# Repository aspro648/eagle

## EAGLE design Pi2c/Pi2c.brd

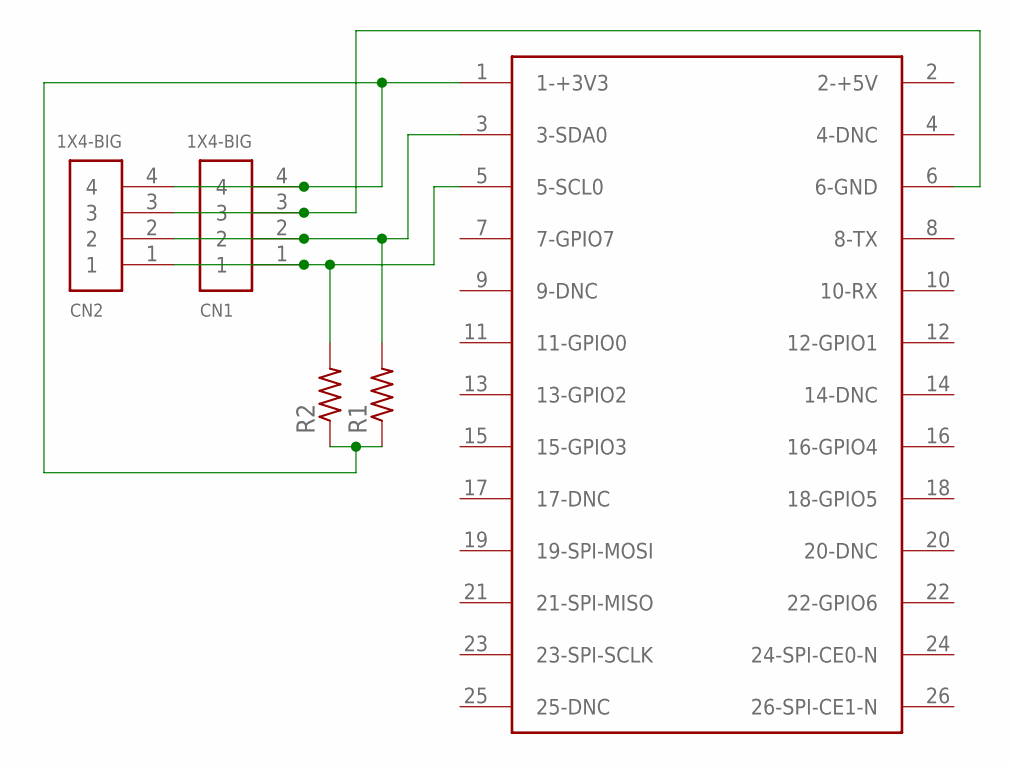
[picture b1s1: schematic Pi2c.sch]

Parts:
CN1, CN2: 1X4-BIG; 1X04-BIG
R1, R2: R-US_0207/7; 0207/7
U$1: RASPBERRY-PI

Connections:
unnamed: CN1.4, CN2.4, R1.1, R2.1, U$1.1 (1-+3V3)
unnamed: CN1.3, CN2.3, U$1.6 (6-GND)
unnamed: CN1.2, CN2.2, R1.2, U$1.3 (3-SDA0)
unnamed: CN1.1, CN2.1, R2.2, U$1.5 (5-SCL0)

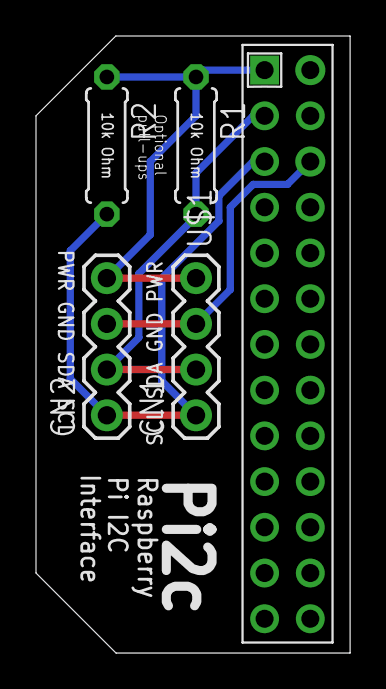
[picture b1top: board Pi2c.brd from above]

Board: 2 copper layers, 17.5 x 34.3 mm, 5 parts (0 on the bottom side), 4 nets.

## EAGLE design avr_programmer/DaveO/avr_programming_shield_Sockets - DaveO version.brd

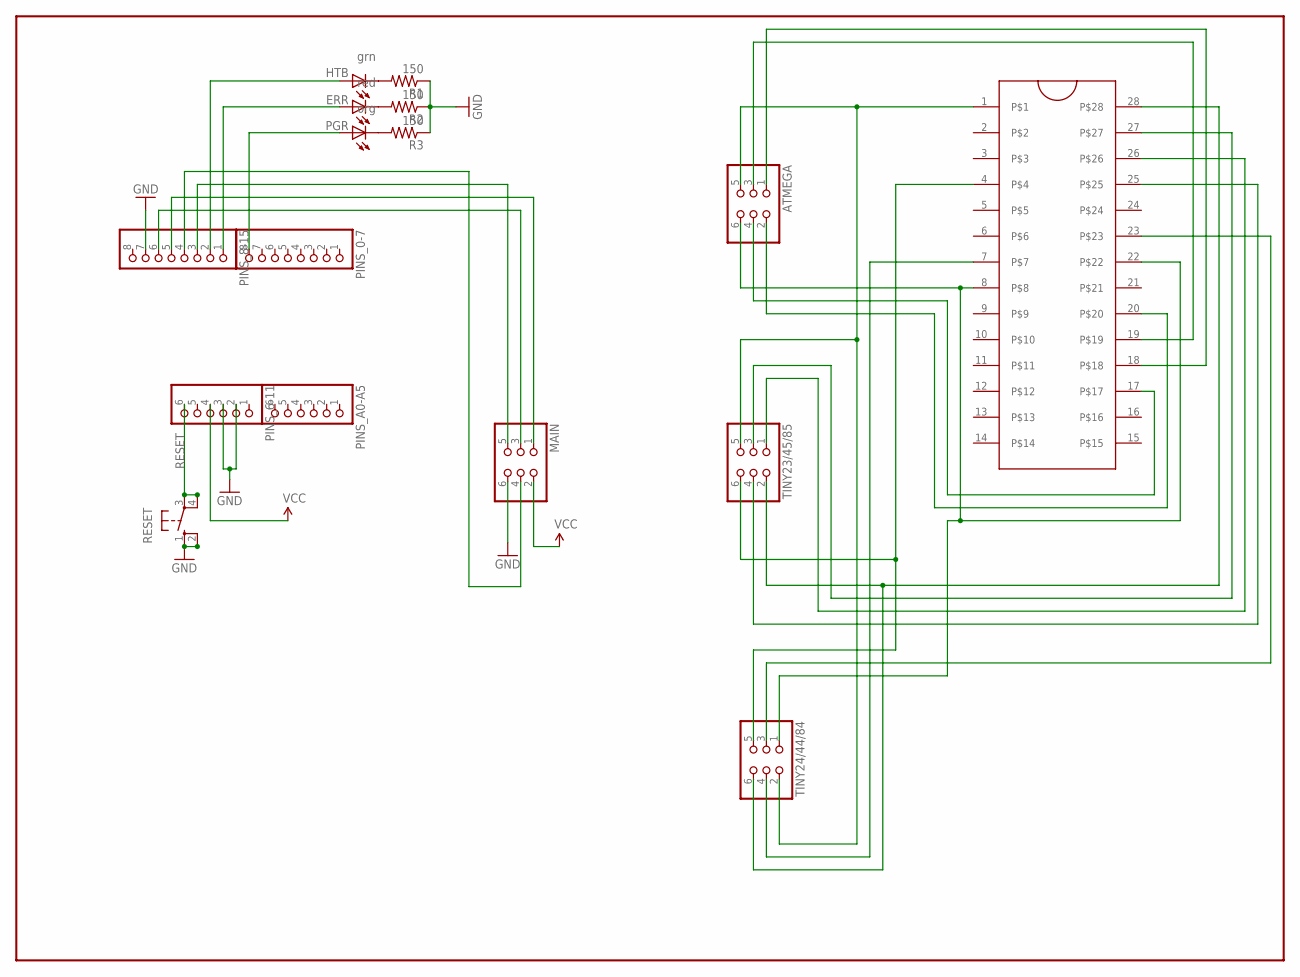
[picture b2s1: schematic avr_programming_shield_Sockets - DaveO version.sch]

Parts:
ATMEGA: PINHD-2X3; 2X03
ERR: red; LED3MM
HTB: grn; LED3MM
MAIN: PINHD-2X3; 2X03
PGR: org; LED3MM
PINS_0-7, PINS_8-15: PINHD-1X8BIG; 1X08-BIG
PINS_6-11: PINHD-1X6B; 1X06-BIG
PINS_A0-A5: PINHD-1X6B; 1X06-BIG
R1, R2, R3: 150; 0204V
RESET: 10-XX; B3F-10XX
TINY23/45/85, TINY24/44/84: PINHD-2X3; 2X03
U$2: ZIFSOCKET-28-3ZIFFSOCKET-28-3; DIL28-3-ZIF_SOCKET

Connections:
328-GND: ATMEGA.6, TINY24/44/84.1, U$2.8, U$2.22
328-MISO: ATMEGA.1, U$2.18
328-SCK: ATMEGA.3, U$2.19
328-VCC: ATMEGA.2, U$2.20
GND: MAIN.6, PINS_6-11.2, PINS_6-11.3, PINS_8-15.7, R1.1, R2.1, R3.1, RESET.1 (S), RESET.2 (S1)
MISO: MAIN.1, PINS_8-15.5
MOSI: MAIN.4, PINS_8-15.4
unnamed: TINY23/45/85.3, U$2.27
unnamed: TINY23/45/85.6, TINY24/44/84.5, U$2.4
unnamed: ATMEGA.4, U$2.17
unnamed: TINY23/45/85.4, U$2.25
unnamed: ATMEGA.5, TINY23/45/85.5, TINY24/44/84.2, U$2.1
unnamed: ERR.A, PINS_8-15.1
unnamed: TINY23/45/85.2, TINY24/44/84.6, U$2.28
unnamed: HTB.K (C), R1.2
unnamed: ERR.K (C), R2.2
unnamed: PGR.K (C), R3.2
unnamed: TINY23/45/85.1, U$2.26
unnamed: PGR.A, PINS_0-7.8
unnamed: HTB.A, PINS_8-15.2
unnamed: TINY24/44/84.3, U$2.23
unnamed: TINY24/44/84.4, U$2.7
RESET: PINS_6-11.6, RESET.3, RESET.4 (P1)
RST: MAIN.5, PINS_8-15.3
SCK: MAIN.3, PINS_8-15.6
VCC: MAIN.2, PINS_6-11.4

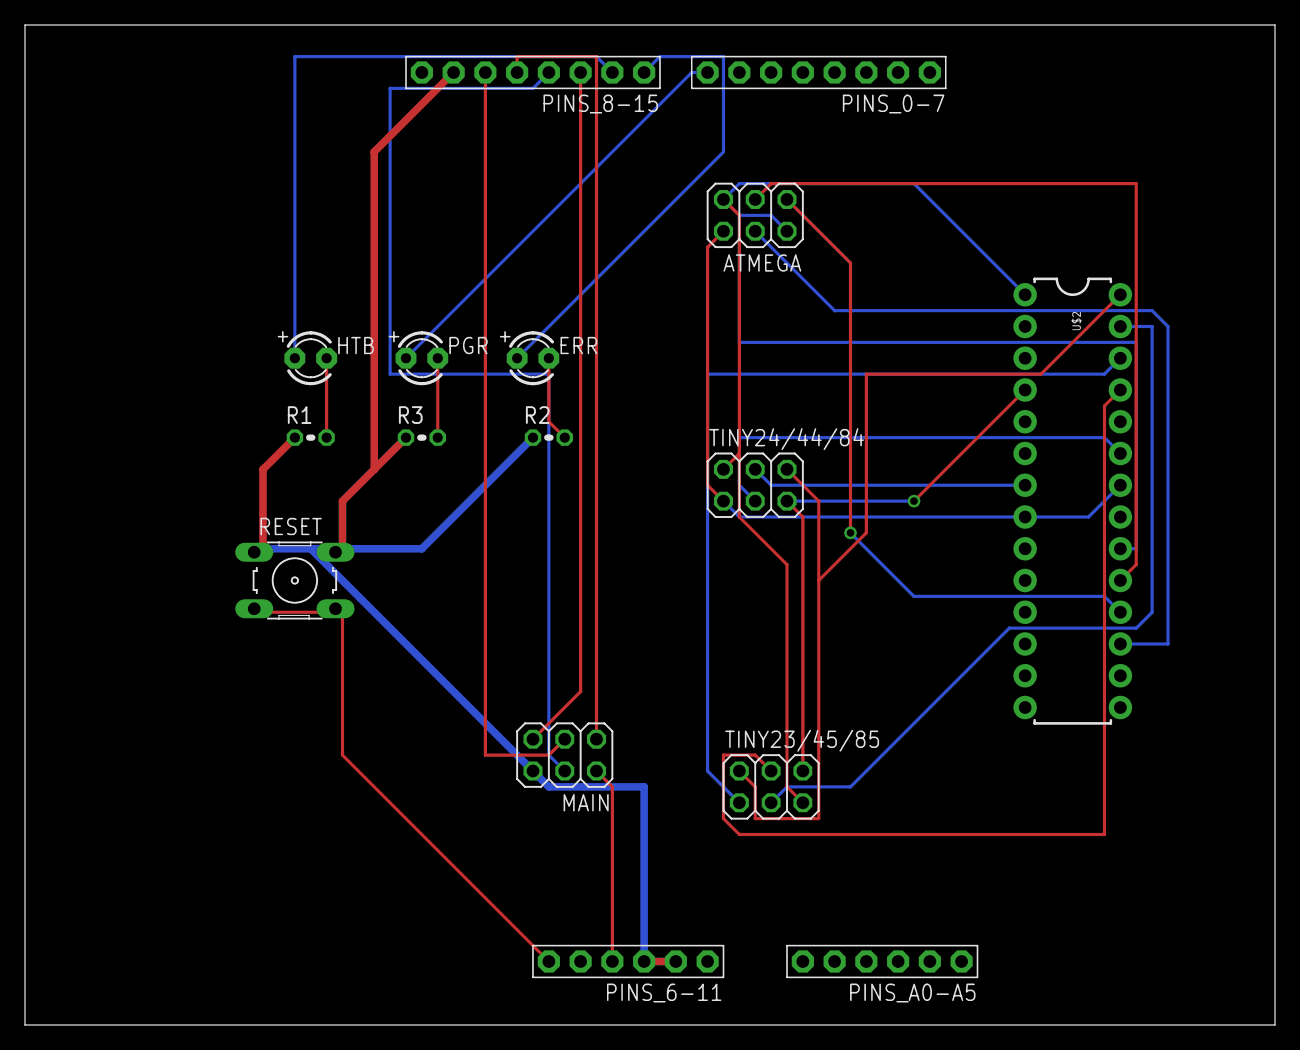
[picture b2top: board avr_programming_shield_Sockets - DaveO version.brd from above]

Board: 2 copper layers, 100.0 x 80.0 mm, 16 parts (0 on the bottom side), 26 nets.

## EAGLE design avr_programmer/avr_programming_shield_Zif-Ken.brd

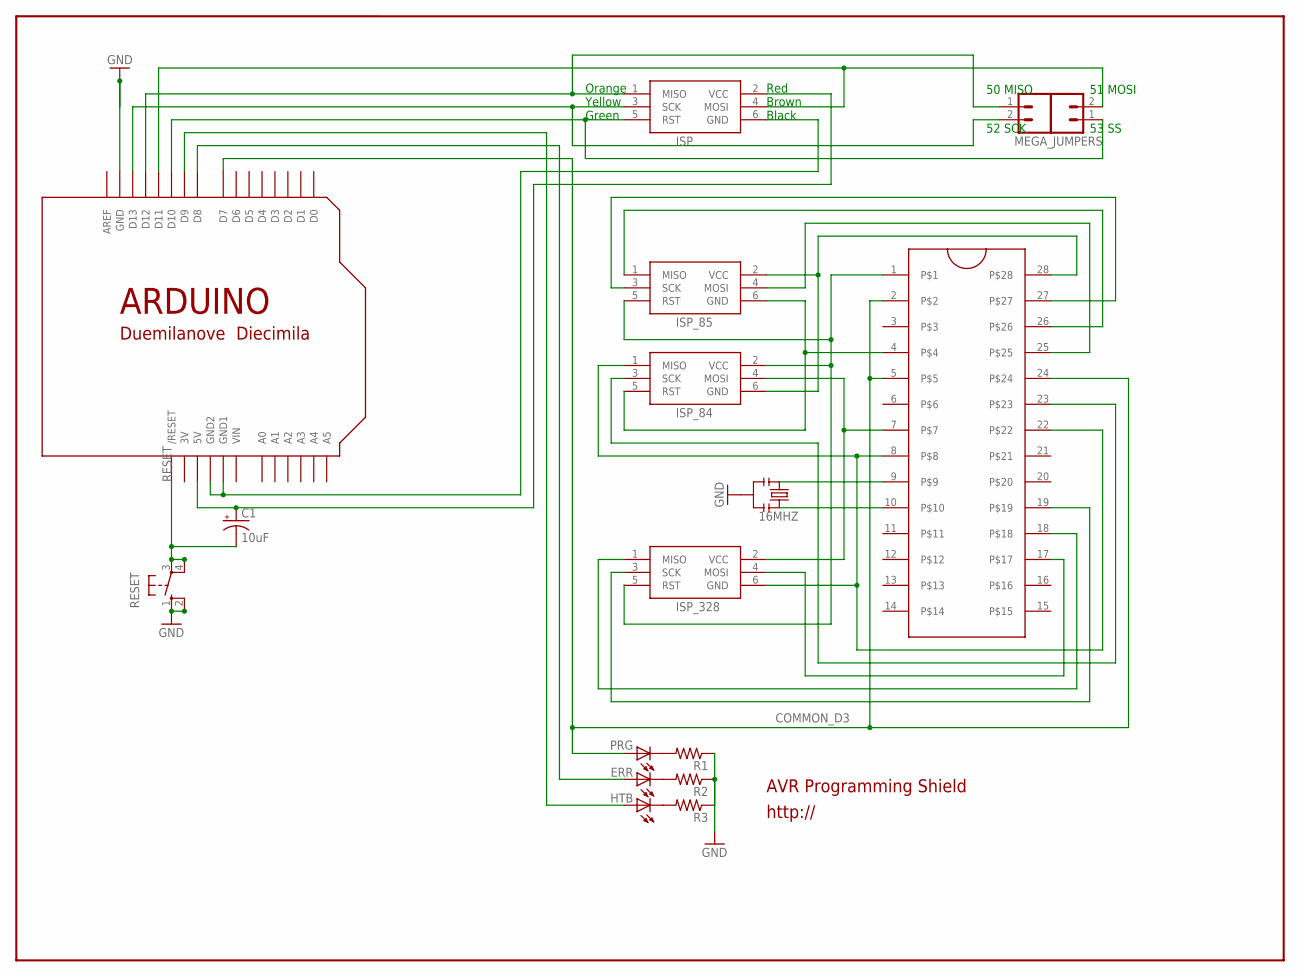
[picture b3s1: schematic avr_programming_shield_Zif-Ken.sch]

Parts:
16MHZ: RESONATORPTH; RESONATOR-PTH
C1: 10uF; CPOL-RADIAL-10UF-25V
ERR: LED3MM
HTB: LED3MM
ISP: AVRISP-6; AVRISP
ISP_84, ISP_85, ISP_328: AVRISP-6; AVRISP
JP2: M02PTH; 1X02
MEGA_JUMPERS: M02PTH; 1X02
PRG: LED3MM
R1, R2, R3: R-US_0204/2V; 0204V
RESET: 10-XX; B3F-10XX
U$1: ARDUINO-NOHOLE
U$3: ZIFSOCKET-28-3ZIFFSOCKET-28-3; DIL28-3-ZIF_SOCKET

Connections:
3V: U$1.3V
COMMON_D3: PRG.A, U$1.D7, U$3.2, U$3.5, U$3.24
GND: 16MHZ.2, ISP.6 (GND), R1.1, R2.1, R3.1, RESET.1 (S), RESET.2 (S1), U$1.GND, U$1.GND1, U$1.GND2
unnamed: ISP_328.4 (MOSI), U$3.17
unnamed: ISP.3 (SCK), MEGA_JUMPERS.2, U$1.D13
unnamed: ISP.1 (MISO), MEGA_JUMPERS.1, U$1.D12
unnamed: ISP_328.1 (MISO), U$3.18
unnamed: ISP.5 (RST), JP2.1, U$1.D10
unnamed: ISP.4 (MOSI), JP2.2, U$1.D11
unnamed: ISP_328.3 (SCK), U$3.19
unnamed: PRG.K (C), R1.2
unnamed: ERR.K (C), R2.2
unnamed: HTB.K (C), R3.2
unnamed: ISP_84.4 (MOSI), ISP_328.2 (VCC), U$3.7
unnamed: ISP_84.2 (VCC), ISP_85.5 (RST), ISP_328.5 (RST), U$3.1
unnamed: ISP_84.3 (SCK), U$3.23
unnamed: ISP_84.6 (GND), ISP_85.2 (VCC), U$3.28
unnamed: HTB.A, U$1.D9
unnamed: ISP_84.5 (RST), ISP_85.6 (GND), U$3.4
unnamed: ISP_85.4 (MOSI), U$3.25
unnamed: ISP_85.1 (MISO), U$3.26
unnamed: ISP_85.3 (SCK), U$3.27
unnamed: 16MHZ.1, U$3.9
unnamed: ERR.A, U$1.D8
unnamed: 16MHZ.3, U$3.10
unnamed: ISP_84.1 (MISO), ISP_328.6 (GND), U$3.8, U$3.22
RESET: C1.2 (-), RESET.3, RESET.4 (P1), U$1.RESET (/RESET)
VCC: C1.1 (+), ISP.2 (VCC), U$1.5V
VIN: U$1.VIN

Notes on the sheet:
AVR Programming Shield
http://
Red Brown Black
Orange Yellow Green
50 MISO
51 MOSI
53 SS
52 SCK

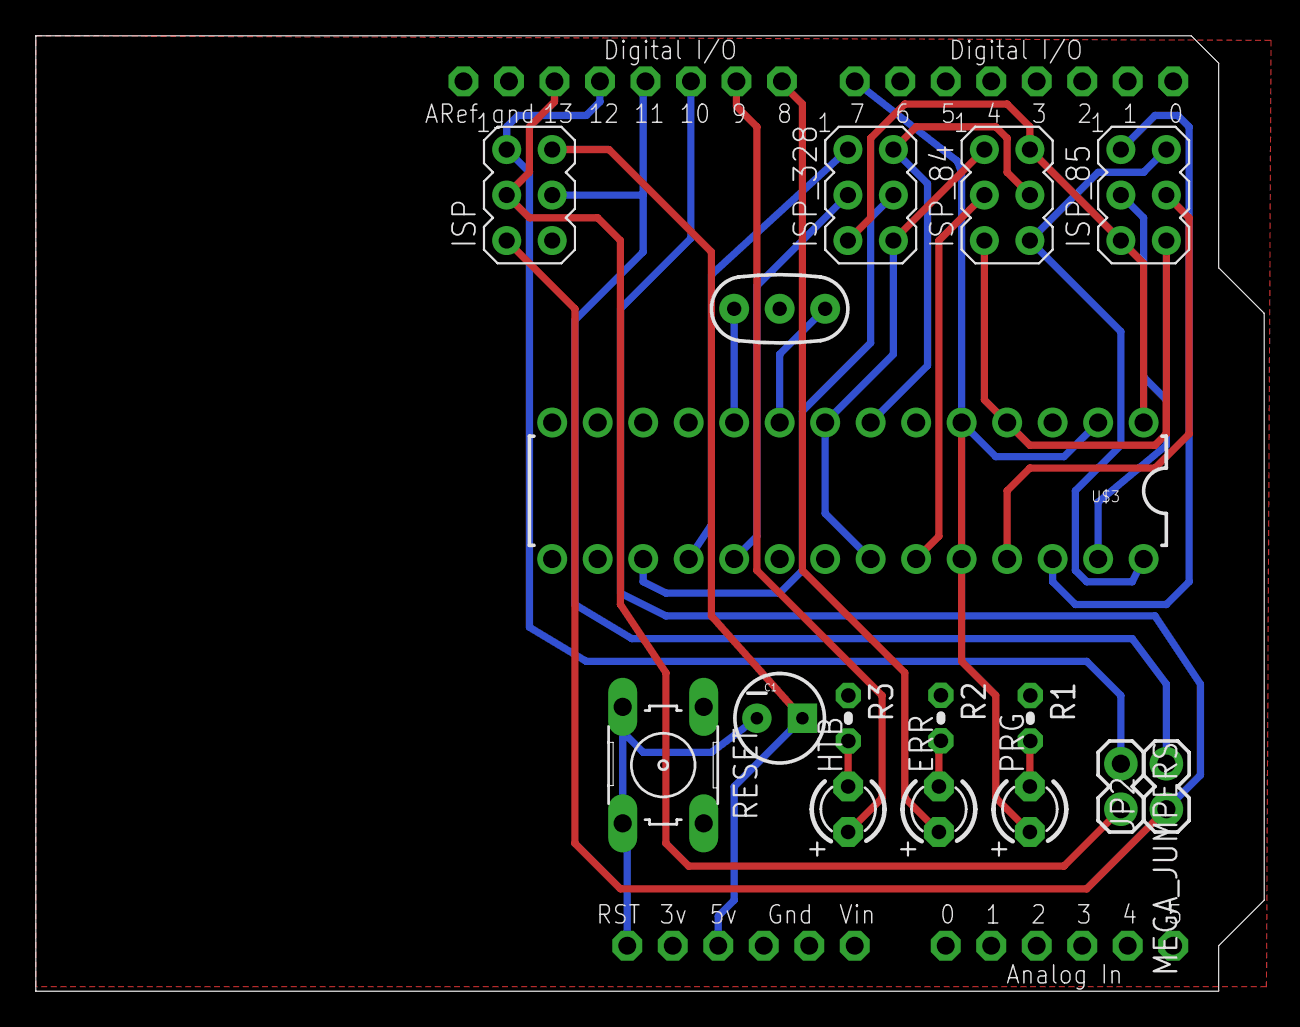
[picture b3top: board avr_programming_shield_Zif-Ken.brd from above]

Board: 2 copper layers, 68.6 x 53.3 mm, 18 parts (0 on the bottom side), 27 nets.

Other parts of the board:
E$1: OSHWLOGO_TOL_0.2

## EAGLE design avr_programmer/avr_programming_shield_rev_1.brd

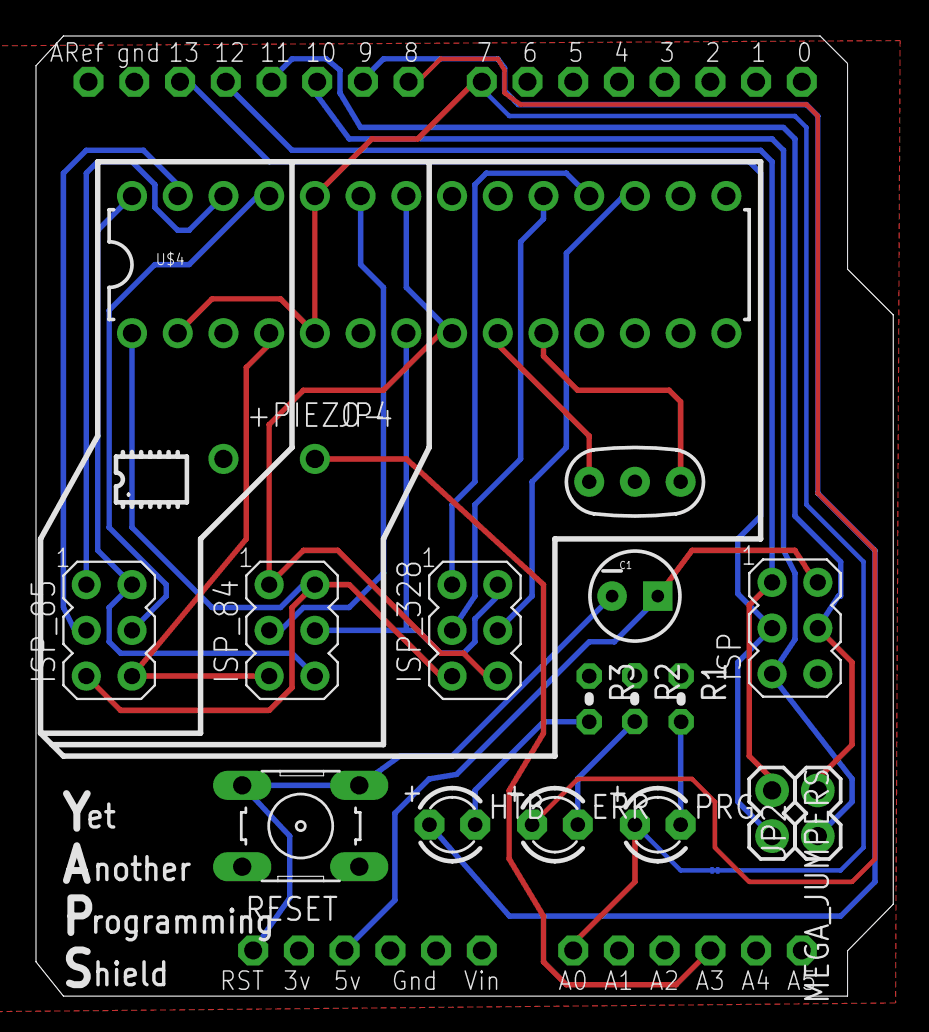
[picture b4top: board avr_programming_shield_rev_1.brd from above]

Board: 2 copper layers, 47.6 x 53.3 mm, 20 parts (0 on the bottom side), 28 nets.

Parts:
16MHZ: RESONATORPTH; RESONATOR-PTH
+PIEZO-: M01PTH; 1X01
C1: 10uF; CPOL-RADIAL-10UF-25V
ERR: LED3MM
HTB: LED3MM
ISP: AVRISP-6; AVRISP
ISP_84, ISP_85, ISP_328: AVRISP-6; AVRISP
JP2: 1X02
JP4: M01PTH; 1X01
MEGA_JUMPERS: 1X02
PRG: LED3MM
R1, R2, R3: 0204V
RESET: B3F-10XX
U$2: OSHWLOGO_BOTTOM
U$4: ZIFSOCKET-28-3ZIFFSOCKET-28-3; DIL28-3-ZIF_SOCKET
U$5: ARDUINO-NOHOLE

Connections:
COMMON_D3: PRG.A, U$4.2, U$4.5, U$4.24, U$5.A0, U$5.D7
GND: 16MHZ.2, +PIEZO-.1, ISP.6, R1.1, R2.1, R3.1, RESET.1, RESET.2, U$5.GND, U$5.GND1, U$5.GND2
unnamed: ISP_328.4, U$4.17
unnamed: ISP.3, MEGA_JUMPERS.2, U$5.D13
unnamed: ISP.1, MEGA_JUMPERS.1, U$5.D12
unnamed: ISP_328.1, U$4.18
unnamed: ISP.5, JP2.1, U$5.D10
unnamed: ISP.4, JP2.2, U$5.D11
unnamed: ISP_328.3, U$4.19
unnamed: PRG.K, R1.2
unnamed: ERR.K, R2.2
unnamed: HTB.K, R3.2
unnamed: ISP_84.4, ISP_328.2, U$4.7
unnamed: JP4.1, U$5.A3
unnamed: ISP_84.2, ISP_85.5, ISP_328.5, U$4.1
unnamed: ISP_84.3, U$4.23
unnamed: ISP_84.6, ISP_85.2, U$4.28
unnamed: HTB.A, U$5.D9
unnamed: ISP_84.5, ISP_85.6, U$4.4
unnamed: ISP_85.4, U$4.25
unnamed: ISP_85.1, U$4.26
unnamed: ISP_85.3, U$4.27
unnamed: 16MHZ.1, U$4.9
unnamed: ERR.A, U$5.D8
unnamed: 16MHZ.3, U$4.10
unnamed: ISP_84.1, ISP_328.6, U$4.8, U$4.22
RESET: C1.2, RESET.3, RESET.4, U$5.RESET
VCC: C1.1, ISP.2, U$5.5V

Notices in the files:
parts and their libraries:
SparkFun-Connectors: Licensing: CC v3.0 Share-Alike You are welcome to use this library for commercial purposes.
